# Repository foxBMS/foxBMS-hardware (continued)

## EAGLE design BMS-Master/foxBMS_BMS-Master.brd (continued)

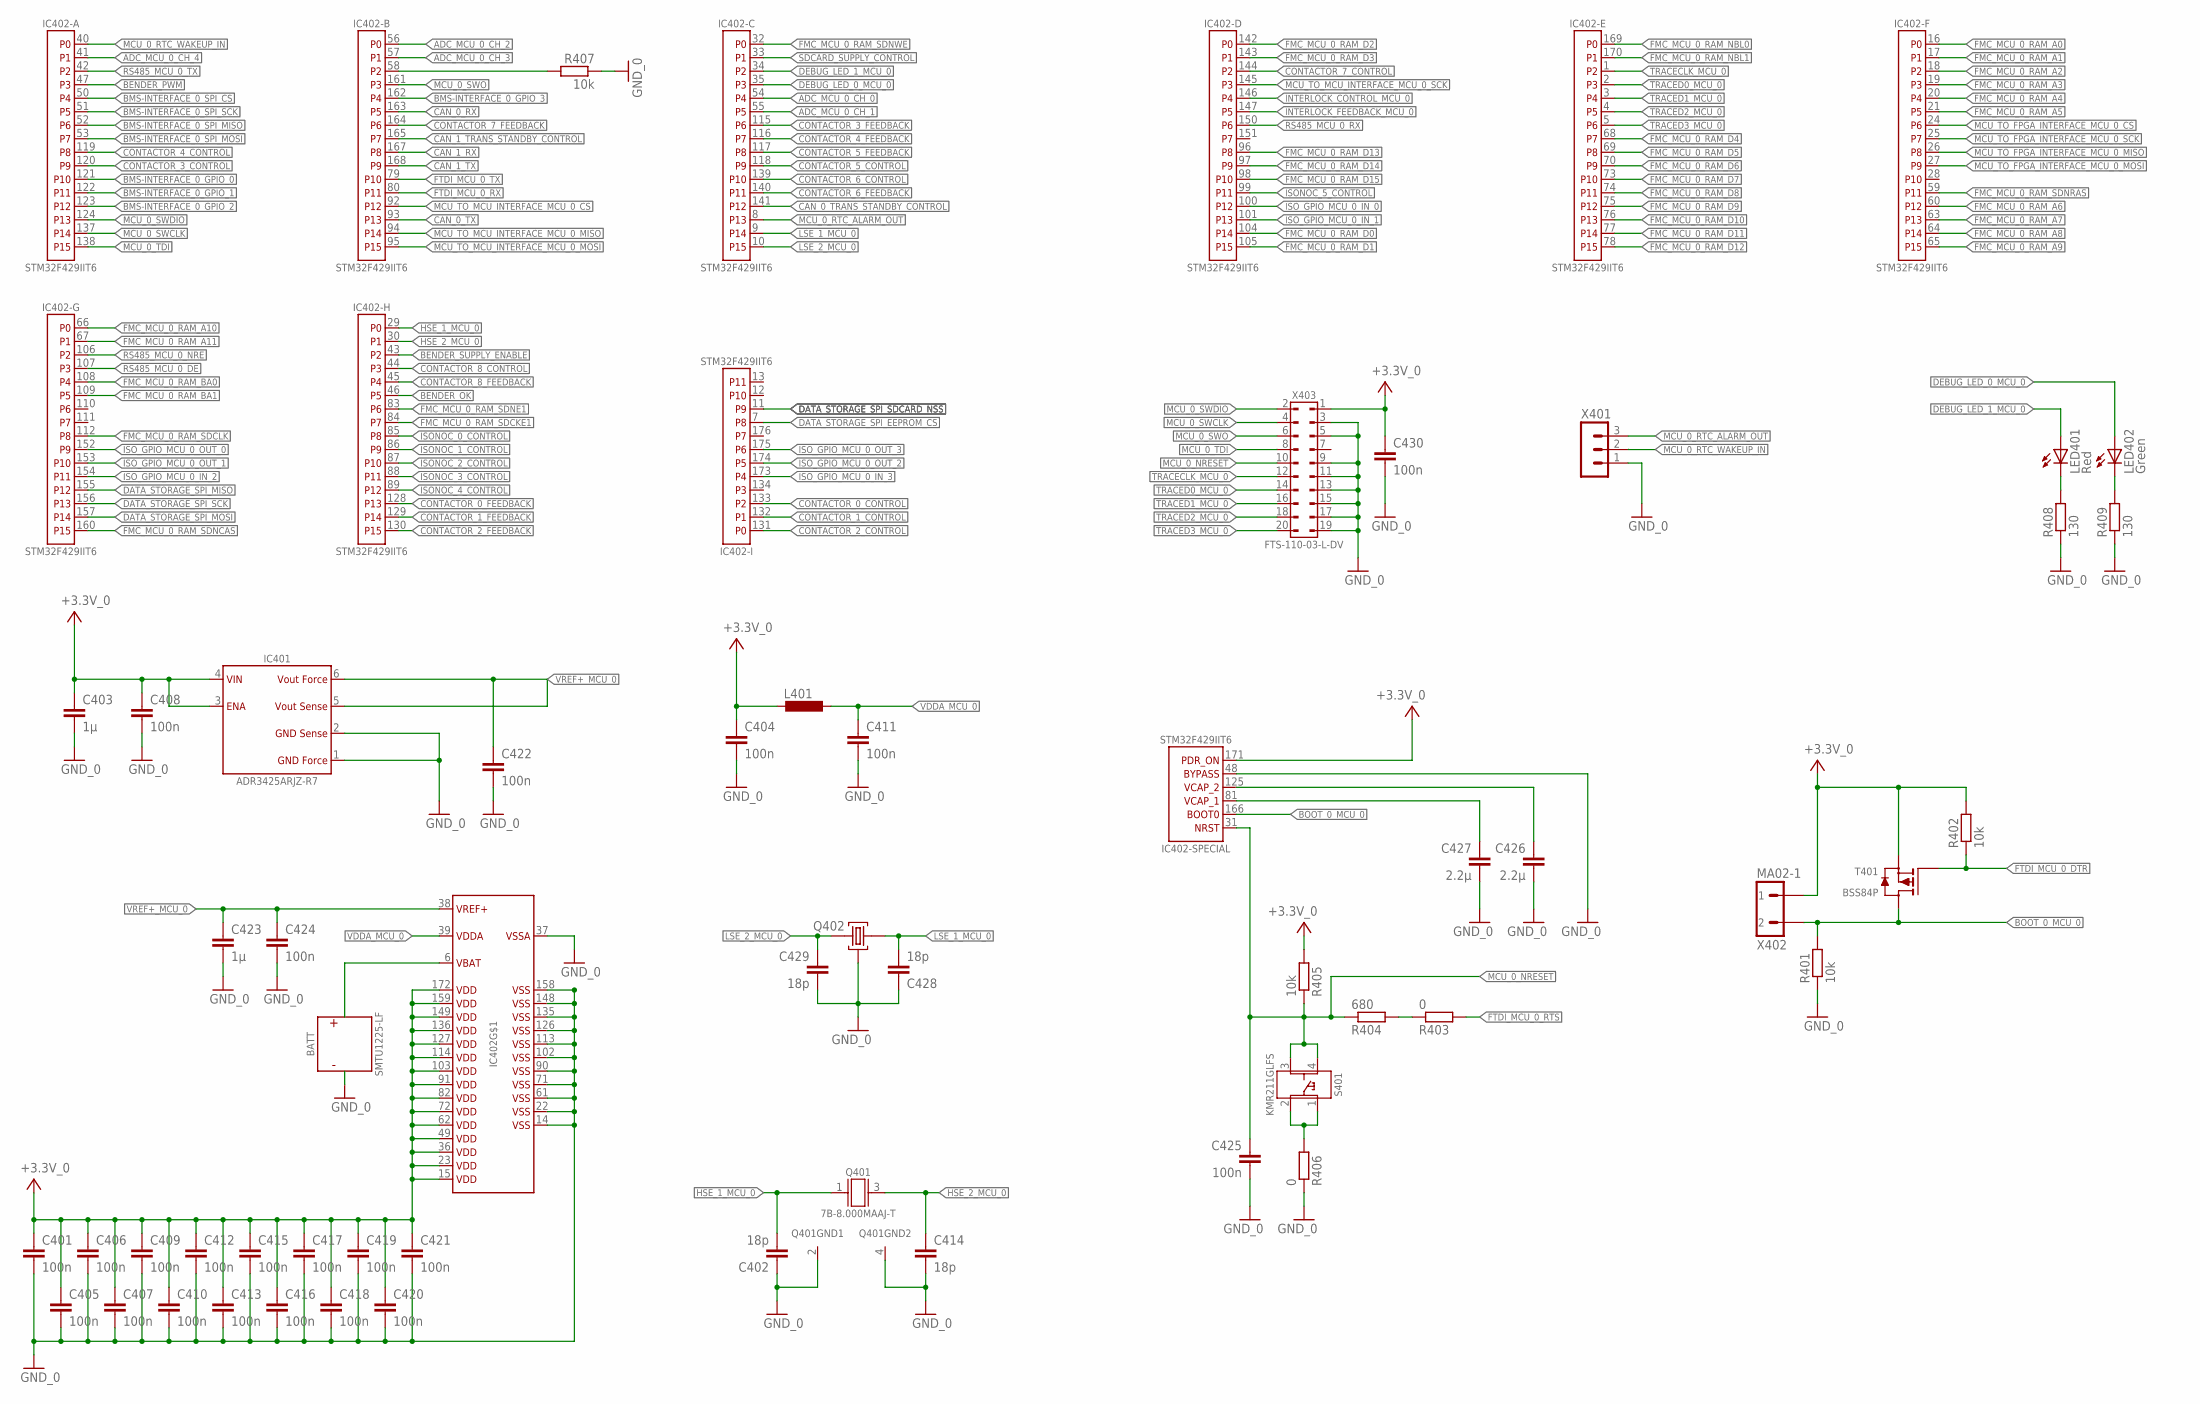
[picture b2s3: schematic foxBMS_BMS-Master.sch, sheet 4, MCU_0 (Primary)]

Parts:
BATT: SMTU1225-LF; X_SMD_(23,70MM_X_12,70MM_X_5,00MM)_R_RENATA_REV01
C401, C404, C405, C406, C407, C408, C409, C410, C411, C412, C413, C415, C416, C417, C418, C419, C420, C421, C422, C424, C425, C430: 100n; C0603
C402, C414, C428, C429: 18p; C0603
C403, C423: 1µ; C0603
C426, C427: 2.2µ; C0603
IC401: ADR3425ARJZ; IC_SMD_SOT23-6_(MO-178-AB)_R_AD_REV01
IC402: STM32F429IIT6; IC_SMD_LQFP176_R_ST_REV01
L401: L0805; 0805
LED401: Red; CHIP-LED0603
LED402: Green; CHIP-LED0603
Q401: 7B-8.000MAAJ-T; G_SMD_5,00MM_X_3,20MM_0,90MM_(7B)_TXC_REV01
Q402: MS3V; MS3V-T1R
R401, R402, R405, R407: 10k; R0603
R403, R406: 0; R0603
R404: 680; R0603
R408, R409: 130; R0603
S401: KMR211GLFS; S_SMD_4,60MMX2,80MMX1,90MM_R_CK-COMPONENTS_REV01
T401: BSS84P; V_SMD_SOT23_(TO-236AB)_R_INFINEON_REV01
X401: MA03-1
X402: MA02-1
X403: SAMTEC_FTS_20POL_HEADER_VERTIKAL_REV01; X_SMD_FTS_110-03_(20POL)_R_SAMTEC_REV01

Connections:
+3.3V_0: C401.1, C403.1, C404.1, C405.1, C406.1, C407.1, C408.1, C409.1, C410.1, C412.1, C413.1, C415.1, C416.1, C417.1, C418.1, C419.1, C420.1, C421.1, C430.1, IC401.3 (ENABLE), IC401.4 (VIN), IC402.15 (VDD1), IC402.23 (VDD2), IC402.36 (VDD3), IC402.49 (VDD4), IC402.62 (VDD5), IC402.72 (VDD6), IC402.82 (VDD7), IC402.91 (VDD8), IC402.103 (VDD9), IC402.114 (VDD10), IC402.127 (VDD11), IC402.136 (VDD12), IC402.149 (VDD13), IC402.159 (VDD14), IC402.171 (PDR_ON), IC402.172 (VDD15), L401.1, R402.2, R405.2, T401.2 (S), X402.1, X403.1; also elsewhere on the board
ADC_MCU_0_CH_0: IC402.54 (P4); also elsewhere on the board
ADC_MCU_0_CH_1: IC402.55 (P5); also elsewhere on the board
ADC_MCU_0_CH_2: IC402.56 (P0); also elsewhere on the board
ADC_MCU_0_CH_3: IC402.57 (P1); also elsewhere on the board
ADC_MCU_0_CH_4: IC402.41 (P1); also elsewhere on the board
BENDER_OK: IC402.46 (P5); also elsewhere on the board
BENDER_PWM: IC402.47 (P3); also elsewhere on the board
BENDER_SUPPLY_ENABLE: IC402.43 (P2); also elsewhere on the board
BMS-INTERFACE_0_GPIO_0: IC402.121 (P10); also elsewhere on the board
BMS-INTERFACE_0_GPIO_1: IC402.122 (P11); also elsewhere on the board
BMS-INTERFACE_0_GPIO_2: IC402.123 (P12); also elsewhere on the board
BMS-INTERFACE_0_GPIO_3: IC402.162 (P4); also elsewhere on the board
BMS-INTERFACE_0_SPI_CS: IC402.50 (P4); also elsewhere on the board
BMS-INTERFACE_0_SPI_MISO: IC402.52 (P6); also elsewhere on the board
BMS-INTERFACE_0_SPI_MOSI: IC402.53 (P7); also elsewhere on the board
BMS-INTERFACE_0_SPI_SCK: IC402.51 (P5); also elsewhere on the board
BOOT_0_MCU_0: IC402.166 (BOOT0), R401.2, T401.3 (D), X402.2
CAN_0_RX: IC402.163 (P5); also elsewhere on the board
CAN_0_TRANS_STANDBY_CONTROL: IC402.141 (P12); also elsewhere on the board
CAN_0_TX: IC402.93 (P13); also elsewhere on the board
CAN_1_RX: IC402.167 (P8); also elsewhere on the board
CAN_1_TRANS_STANDBY_CONTROL: IC402.165 (P7); also elsewhere on the board
CAN_1_TX: IC402.168 (P9); also elsewhere on the board
CONTACTOR_0_CONTROL: IC402.133 (P2); also elsewhere on the board
CONTACTOR_0_FEEDBACK: IC402.128 (P13); also elsewhere on the board
CONTACTOR_1_CONTROL: IC402.132 (P1); also elsewhere on the board
CONTACTOR_1_FEEDBACK: IC402.129 (P14); also elsewhere on the board
CONTACTOR_2_CONTROL: IC402.131 (P0); also elsewhere on the board
CONTACTOR_2_FEEDBACK: IC402.130 (P15); also elsewhere on the board
CONTACTOR_3_CONTROL: IC402.120 (P9); also elsewhere on the board
CONTACTOR_3_FEEDBACK: IC402.115 (P6); also elsewhere on the board
CONTACTOR_4_CONTROL: IC402.119 (P8); also elsewhere on the board
CONTACTOR_4_FEEDBACK: IC402.116 (P7); also elsewhere on the board
CONTACTOR_5_CONTROL: IC402.118 (P9); also elsewhere on the board
CONTACTOR_5_FEEDBACK: IC402.117 (P8); also elsewhere on the board
CONTACTOR_6_CONTROL: IC402.139 (P10); also elsewhere on the board
CONTACTOR_6_FEEDBACK: IC402.140 (P11); also elsewhere on the board
CONTACTOR_7_CONTROL: IC402.144 (P2); also elsewhere on the board
CONTACTOR_7_FEEDBACK: IC402.164 (P6); also elsewhere on the board
CONTACTOR_8_CONTROL: IC402.44 (P3); also elsewhere on the board
CONTACTOR_8_FEEDBACK: IC402.45 (P4); also elsewhere on the board
DATA_STORAGE_SPI_EEPROM_CS: IC402.7 (P8); also elsewhere on the board
DATA_STORAGE_SPI_MISO: IC402.155 (P12); also elsewhere on the board
DATA_STORAGE_SPI_MOSI: IC402.157 (P14); also elsewhere on the board
DATA_STORAGE_SPI_SCK: IC402.156 (P13); also elsewhere on the board
DATA_STORAGE_SPI_SDCARD_NSS: IC402.11 (P9); also elsewhere on the board
DEBUG_LED_0_MCU_0: IC402.35 (P3), LED402.A
DEBUG_LED_1_MCU_0: IC402.34 (P2), LED401.A
FMC_MCU_0_RAM_A0: IC402.16 (P0); also elsewhere on the board
FMC_MCU_0_RAM_A1: IC402.17 (P1); also elsewhere on the board
FMC_MCU_0_RAM_A2: IC402.18 (P2); also elsewhere on the board
FMC_MCU_0_RAM_A3: IC402.19 (P3); also elsewhere on the board
FMC_MCU_0_RAM_A4: IC402.20 (P4); also elsewhere on the board
FMC_MCU_0_RAM_A5: IC402.21 (P5); also elsewhere on the board
FMC_MCU_0_RAM_A6: IC402.60 (P12); also elsewhere on the board
FMC_MCU_0_RAM_A7: IC402.63 (P13); also elsewhere on the board
FMC_MCU_0_RAM_A8: IC402.64 (P14); also elsewhere on the board
FMC_MCU_0_RAM_A9: IC402.65 (P15); also elsewhere on the board
FMC_MCU_0_RAM_A10: IC402.66 (P0); also elsewhere on the board
FMC_MCU_0_RAM_A11: IC402.67 (P1); also elsewhere on the board
FMC_MCU_0_RAM_BA0: IC402.108 (P4); also elsewhere on the board
FMC_MCU_0_RAM_BA1: IC402.109 (P5); also elsewhere on the board
FMC_MCU_0_RAM_D0: IC402.104 (P14); also elsewhere on the board
FMC_MCU_0_RAM_D1: IC402.105 (P15); also elsewhere on the board
FMC_MCU_0_RAM_D2: IC402.142 (P0); also elsewhere on the board
FMC_MCU_0_RAM_D3: IC402.143 (P1); also elsewhere on the board
FMC_MCU_0_RAM_D4: IC402.68 (P7); also elsewhere on the board
FMC_MCU_0_RAM_D5: IC402.69 (P8); also elsewhere on the board
FMC_MCU_0_RAM_D6: IC402.70 (P9); also elsewhere on the board
FMC_MCU_0_RAM_D7: IC402.73 (P10); also elsewhere on the board
FMC_MCU_0_RAM_D8: IC402.74 (P11); also elsewhere on the board
FMC_MCU_0_RAM_D9: IC402.75 (P12); also elsewhere on the board
FMC_MCU_0_RAM_D10: IC402.76 (P13); also elsewhere on the board
FMC_MCU_0_RAM_D11: IC402.77 (P14); also elsewhere on the board
FMC_MCU_0_RAM_D12: IC402.78 (P15); also elsewhere on the board
FMC_MCU_0_RAM_D13: IC402.96 (P8); also elsewhere on the board
FMC_MCU_0_RAM_D14: IC402.97 (P9); also elsewhere on the board
FMC_MCU_0_RAM_D15: IC402.98 (P10); also elsewhere on the board
FMC_MCU_0_RAM_NBL0: IC402.169 (P0); also elsewhere on the board
FMC_MCU_0_RAM_NBL1: IC402.170 (P1); also elsewhere on the board
FMC_MCU_0_RAM_SDCKE1: IC402.84 (P7); also elsewhere on the board
FMC_MCU_0_RAM_SDCLK: IC402.112 (P8); also elsewhere on the board
FMC_MCU_0_RAM_SDNCAS: IC402.160 (P15); also elsewhere on the board
FMC_MCU_0_RAM_SDNE1: IC402.83 (P6); also elsewhere on the board
FMC_MCU_0_RAM_SDNRAS: IC402.59 (P11); also elsewhere on the board
FMC_MCU_0_RAM_SDNWE: IC402.32 (P0); also elsewhere on the board
FTDI_MCU_0_DTR: R402.1, T401.1 (G); also elsewhere on the board
FTDI_MCU_0_RTS: R403.2; also elsewhere on the board
FTDI_MCU_0_RX: IC402.80 (P11); also elsewhere on the board
FTDI_MCU_0_TX: IC402.79 (P10); also elsewhere on the board
GND_0: BATT.-, C401.2, C402.1, C403.2, C404.2, C405.2, C406.2, C407.2, C408.2, C409.2, C410.2, C411.2, C412.2, C413.2, C414.2, C415.2, C416.2, C417.2, C418.2, C419.2, C420.2, C421.2, C422.2, C423.2, C424.2, C425.2, C426.2, C427.2, C428.1, C429.2, C430.2, IC401.1 (GND_FORCE), IC401.2 (GND_SENSE), IC402.14 (VSS1), IC402.22 (VSS2), IC402.37 (VSSA), IC402.48 (BYPASS_REG), IC402.61 (VSS3), IC402.71 (VSS4), IC402.90 (VSS5), IC402.102 (VSS6), IC402.113 (VSS7), IC402.126 (VSS8), IC402.135 (VSS9), IC402.148 (VSS10), IC402.158 (VSS11), Q401.2 (GND), Q401.4 (GND), Q402.P$3 (2), R401.1, R406.1, R407.1, R408.1, R409.1, X401.1, X403.3, X403.5, X403.9, X403.11, X403.13, X403.15, X403.17, X403.19; also elsewhere on the board
HSE_1_MCU_0: C402.2, IC402.29 (P0), Q401.1 (A)
HSE_2_MCU_0: C414.1, IC402.30 (P1), Q401.3 (B)
INTERLOCK_CONTROL_MCU_0: IC402.146 (P4); also elsewhere on the board
INTERLOCK_FEEDBACK_MCU_0: IC402.147 (P5); also elsewhere on the board
ISONOC_0_CONTROL: IC402.85 (P8); also elsewhere on the board
ISONOC_1_CONTROL: IC402.86 (P9); also elsewhere on the board
ISONOC_2_CONTROL: IC402.87 (P10); also elsewhere on the board
ISONOC_3_CONTROL: IC402.88 (P11); also elsewhere on the board
ISONOC_4_CONTROL: IC402.89 (P12); also elsewhere on the board
ISONOC_5_CONTROL: IC402.99 (P11); also elsewhere on the board
ISO_GPIO_MCU_0_IN_0: IC402.100 (P12); also elsewhere on the board
ISO_GPIO_MCU_0_IN_1: IC402.101 (P13); also elsewhere on the board
ISO_GPIO_MCU_0_IN_2: IC402.154 (P11); also elsewhere on the board
ISO_GPIO_MCU_0_IN_3: IC402.173 (P4); also elsewhere on the board
ISO_GPIO_MCU_0_OUT_0: IC402.152 (P9); also elsewhere on the board
ISO_GPIO_MCU_0_OUT_1: IC402.153 (P10); also elsewhere on the board
ISO_GPIO_MCU_0_OUT_2: IC402.174 (P5); also elsewhere on the board
ISO_GPIO_MCU_0_OUT_3: IC402.175 (P6); also elsewhere on the board
LSE_1_MCU_0: C428.2, IC402.9 (P14), Q402.1
LSE_2_MCU_0: C429.1, IC402.10 (P15), Q402.2 (3)
MCU_0_NRESET: C425.1, IC402.31 (NRST), R404.1, R405.1, S401.3, S401.4, X403.10
MCU_0_RTC_ALARM_OUT: IC402.8 (P13), X401.3
MCU_0_RTC_WAKEUP_IN: IC402.40 (P0), X401.2
MCU_0_SWCLK: IC402.137 (P14), X403.4
MCU_0_SWDIO: IC402.124 (P13), X403.2
MCU_0_SWO: IC402.161 (P3), X403.6
MCU_0_TDI: IC402.138 (P15), X403.8
MCU_TO_FPGA_INTERFACE_MCU_0_CS: IC402.24 (P6); also elsewhere on the board
MCU_TO_FPGA_INTERFACE_MCU_0_MISO: IC402.26 (P8); also elsewhere on the board
MCU_TO_FPGA_INTERFACE_MCU_0_MOSI: IC402.27 (P9); also elsewhere on the board
MCU_TO_FPGA_INTERFACE_MCU_0_SCK: IC402.25 (P7); also elsewhere on the board
MCU_TO_MCU_INTERFACE_MCU_0_CS: IC402.92 (P12); also elsewhere on the board
MCU_TO_MCU_INTERFACE_MCU_0_MISO: IC402.94 (P14); also elsewhere on the board
MCU_TO_MCU_INTERFACE_MCU_0_MOSI: IC402.95 (P15); also elsewhere on the board
MCU_TO_MCU_INTERFACE_MCU_0_SCK: IC402.145 (P3); also elsewhere on the board
unnamed: C426.1, IC402.125 (VCAP_2)
unnamed: R406.2, S401.1, S401.2
unnamed: LED401.C, R408.2
unnamed: LED402.C, R409.2
unnamed: C427.1, IC402.81 (VCAP_1)
unnamed: IC402.58 (P2), R407.2
unnamed: R403.1, R404.2
unnamed: BATT.+, IC402.6 (VBAT)
RS485_MCU_0_DE: IC402.107 (P3); also elsewhere on the board
RS485_MCU_0_NRE: IC402.106 (P2); also elsewhere on the board
RS485_MCU_0_RX: IC402.150 (P6); also elsewhere on the board
RS485_MCU_0_TX: IC402.42 (P2); also elsewhere on the board
SDCARD_SUPPLY_CONTROL: IC402.33 (P1); also elsewhere on the board
TRACECLK_MCU_0: IC402.1 (P2), X403.12
TRACED0_MCU_0: IC402.2 (P3), X403.14
TRACED1_MCU_0: IC402.3 (P4), X403.16
TRACED2_MCU_0: IC402.4 (P5), X403.18
TRACED3_MCU_0: IC402.5 (P6), X403.20
VDDA_MCU_0: C411.1, IC402.39 (VDDA), L401.2
VREF+_MCU_0: C422.1, C423.1, C424.1, IC401.5 (VOUT_SENSE), IC401.6 (VOUT_FORCE), IC402.38 (VREF+)

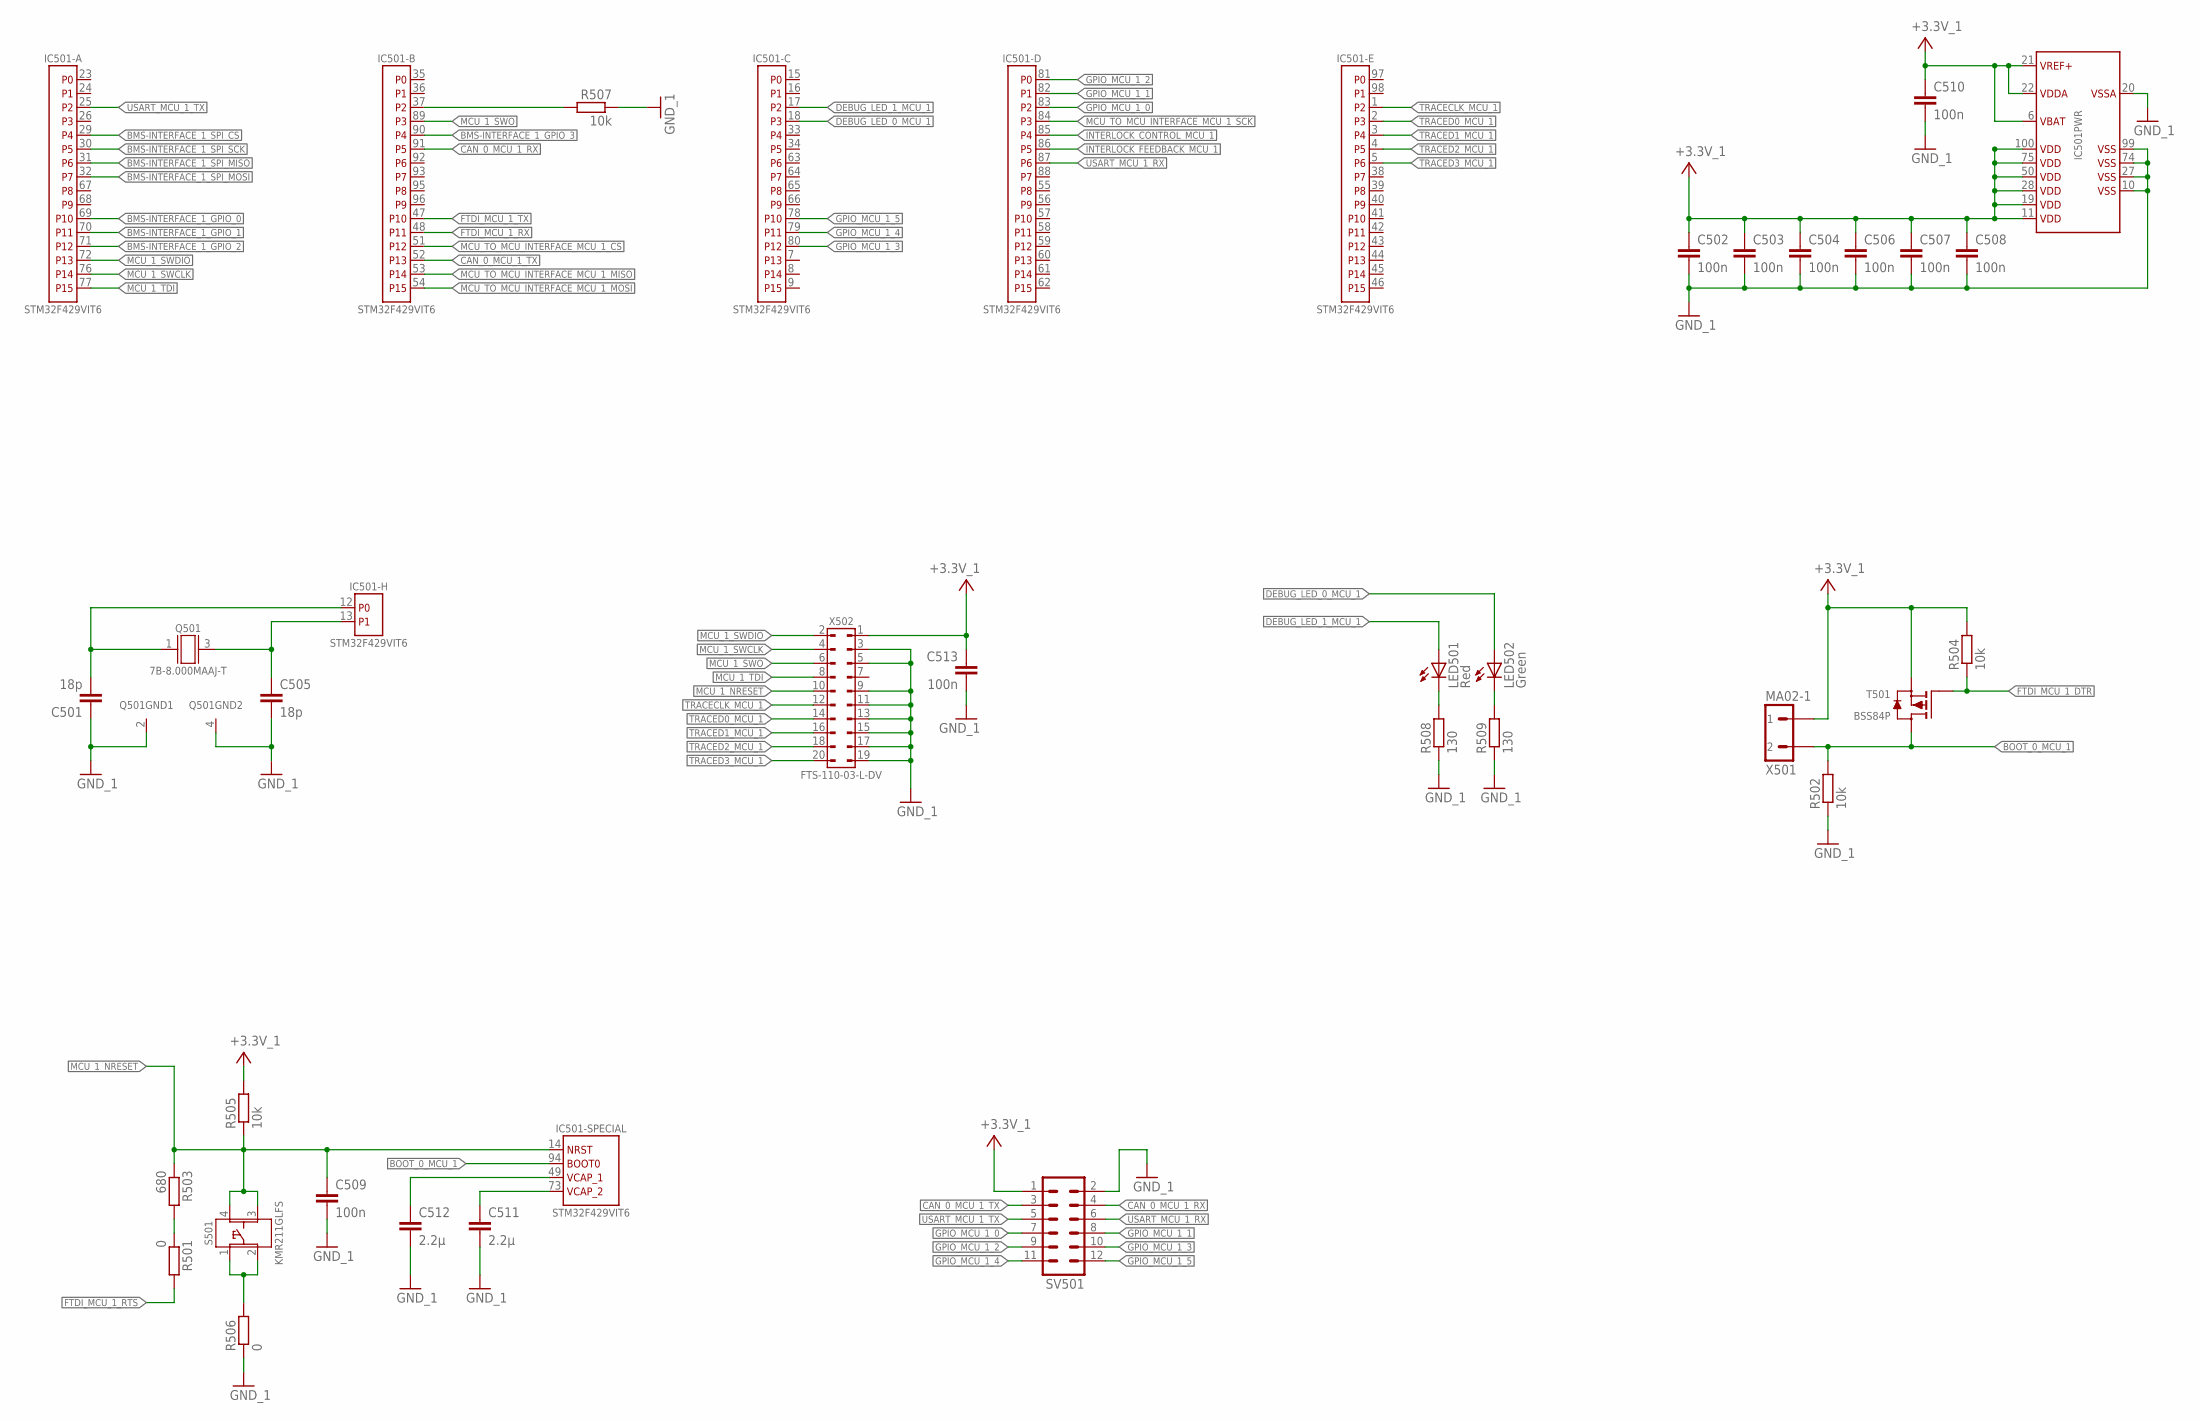
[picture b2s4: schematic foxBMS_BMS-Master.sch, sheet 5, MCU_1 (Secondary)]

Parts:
C501, C505: 18p; C0603
C502, C503, C504, C506, C507, C508, C509, C510, C513: 100n; C0603
C511, C512: 2.2µ; C0603
IC501: STM32F429VIT6; IC_SMD_LQFP100_R_ST_REV01
LED501: Red; CHIP-LED0603
LED502: Green; CHIP-LED0603
Q501: 7B-8.000MAAJ-T; G_SMD_5,00MM_X_3,20MM_0,90MM_(7B)_TXC_REV01
R501, R506: 0; R0603
R502, R504, R505, R507: 10k; R0603
R503: 680; R0603
R508, R509: 130; R0603
S501: KMR211GLFS; S_SMD_4,60MMX2,80MMX1,90MM_R_CK-COMPONENTS_REV01
SV501: MA06-2
T501: BSS84P; V_SMD_SOT23_(TO-236AB)_R_INFINEON_REV01
X501: MA02-1
X502: SAMTEC_FTS_20POL_HEADER_VERTIKAL_REV01; X_SMD_FTS_110-03_(20POL)_R_SAMTEC_REV01

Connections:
+3.3V_1: C502.1, C503.1, C504.1, C506.1, C507.1, C508.1, C510.1, C513.1, IC501.6 (VBAT), IC501.11 (VDD1), IC501.19 (VDD2), IC501.21 (VREF+), IC501.22 (VDDA), IC501.28 (VDD3), IC501.50 (VDD4), IC501.75 (VDD5), IC501.100 (VDD6), R504.2, R505.2, SV501.1, T501.2 (S), X501.1, X502.1; also elsewhere on the board
BMS-INTERFACE_1_GPIO_0: IC501.69 (P10); also elsewhere on the board
BMS-INTERFACE_1_GPIO_1: IC501.70 (P11); also elsewhere on the board
BMS-INTERFACE_1_GPIO_2: IC501.71 (P12); also elsewhere on the board
BMS-INTERFACE_1_GPIO_3: IC501.90 (P4); also elsewhere on the board
BMS-INTERFACE_1_SPI_CS: IC501.29 (P4); also elsewhere on the board
BMS-INTERFACE_1_SPI_MISO: IC501.31 (P6); also elsewhere on the board
BMS-INTERFACE_1_SPI_MOSI: IC501.32 (P7); also elsewhere on the board
BMS-INTERFACE_1_SPI_SCK: IC501.30 (P5); also elsewhere on the board
BOOT_0_MCU_1: IC501.94 (BOOT0), R502.2, T501.3 (D), X501.2
CAN_0_MCU_1_RX: IC501.91 (P5), SV501.4
CAN_0_MCU_1_TX: IC501.52 (P13), SV501.3
DEBUG_LED_0_MCU_1: IC501.18 (P3), LED502.A
DEBUG_LED_1_MCU_1: IC501.17 (P2), LED501.A
FTDI_MCU_1_DTR: R504.1, T501.1 (G); also elsewhere on the board
FTDI_MCU_1_RTS: R501.2; also elsewhere on the board
FTDI_MCU_1_RX: IC501.48 (P11); also elsewhere on the board
FTDI_MCU_1_TX: IC501.47 (P10); also elsewhere on the board
GND_1: C501.1, C502.2, C503.2, C504.2, C505.2, C506.2, C507.2, C508.2, C509.2, C510.2, C511.2, C512.2, C513.2, IC501.10 (VSS1), IC501.20 (VSSA), IC501.27 (VSS2), IC501.74 (VSS3), IC501.99 (VSS4), Q501.2 (GND), Q501.4 (GND), R502.1, R506.1, R507.1, R508.1, R509.1, SV501.2, X502.3, X502.5, X502.9, X502.11, X502.13, X502.15, X502.17, X502.19; also elsewhere on the board
GPIO_MCU_1_0: IC501.83 (P2), SV501.7
GPIO_MCU_1_1: IC501.82 (P1), SV501.8
GPIO_MCU_1_2: IC501.81 (P0), SV501.9
GPIO_MCU_1_3: IC501.80 (P12), SV501.10
GPIO_MCU_1_4: IC501.79 (P11), SV501.11
GPIO_MCU_1_5: IC501.78 (P10), SV501.12
INTERLOCK_CONTROL_MCU_1: IC501.85 (P4); also elsewhere on the board
INTERLOCK_FEEDBACK_MCU_1: IC501.86 (P5); also elsewhere on the board
MCU_1_NRESET: C509.1, IC501.14 (NRST), R503.1, R505.1, S501.3, S501.4, X502.10
MCU_1_SWCLK: IC501.76 (P14), X502.4
MCU_1_SWDIO: IC501.72 (P13), X502.2
MCU_1_SWO: IC501.89 (P3), X502.6
MCU_1_TDI: IC501.77 (P15), X502.8
MCU_TO_MCU_INTERFACE_MCU_1_CS: IC501.51 (P12); also elsewhere on the board
MCU_TO_MCU_INTERFACE_MCU_1_MISO: IC501.53 (P14); also elsewhere on the board
MCU_TO_MCU_INTERFACE_MCU_1_MOSI: IC501.54 (P15); also elsewhere on the board
MCU_TO_MCU_INTERFACE_MCU_1_SCK: IC501.84 (P3); also elsewhere on the board
unnamed: C501.2, IC501.12 (P0), Q501.1 (A)
unnamed: C505.1, IC501.13 (P1), Q501.3 (B)
unnamed: R506.2, S501.1, S501.2
unnamed: LED502.C, R509.2
unnamed: LED501.C, R508.2
unnamed: C511.1, IC501.73 (VCAP_2)
unnamed: C512.1, IC501.49 (VCAP_1)
unnamed: IC501.37 (P2), R507.2
unnamed: R501.1, R503.2
TRACECLK_MCU_1: IC501.1 (P2), X502.12
TRACED0_MCU_1: IC501.2 (P3), X502.14
TRACED1_MCU_1: IC501.3 (P4), X502.16
TRACED2_MCU_1: IC501.4 (P5), X502.18
TRACED3_MCU_1: IC501.5 (P6), X502.20
USART_MCU_1_RX: IC501.87 (P6), SV501.6
USART_MCU_1_TX: IC501.25 (P2), SV501.5

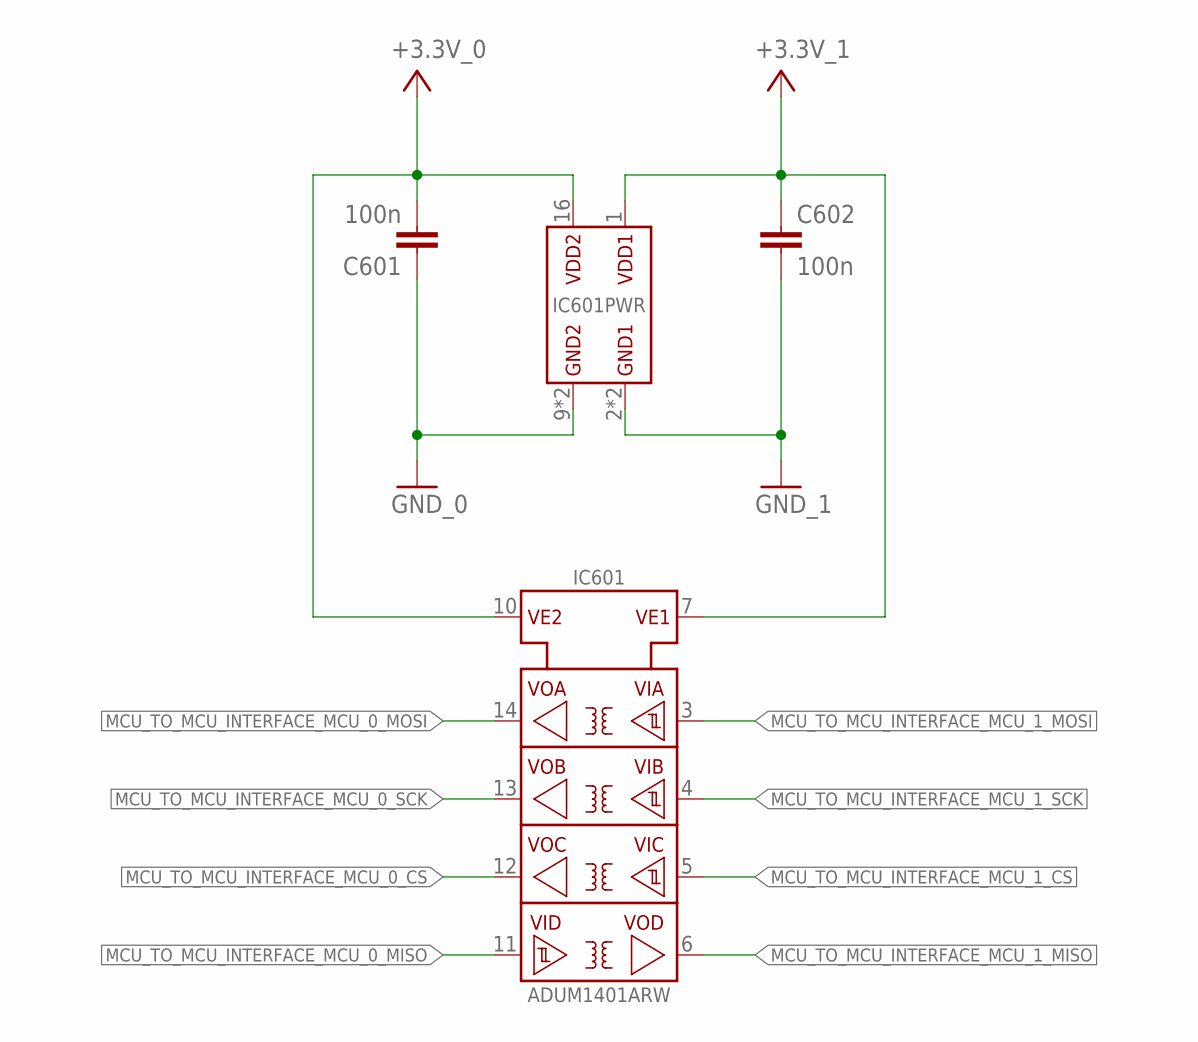
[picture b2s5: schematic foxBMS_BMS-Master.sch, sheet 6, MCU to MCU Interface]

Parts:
C601, C602: 100n; C0603
IC601: ADUM1401ARW; IC_SMD_SOIC-16_(JEDEC_MS-013-AA)_R_ANALOG_REV01

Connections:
+3.3V_0: C601.2, IC601.10 (VE2), IC601.16 (VDD2); also elsewhere on the board
+3.3V_1: C602.1, IC601.1 (VDD1), IC601.7 (VE1); also elsewhere on the board
GND_0: C601.1, IC601.9 (GND2), IC601.15 (GND2); also elsewhere on the board
GND_1: C602.2, IC601.2 (GND1), IC601.8 (GND1); also elsewhere on the board
MCU_TO_MCU_INTERFACE_MCU_0_CS: IC601.12 (VOC); also elsewhere on the board
MCU_TO_MCU_INTERFACE_MCU_0_MISO: IC601.11 (VID); also elsewhere on the board
MCU_TO_MCU_INTERFACE_MCU_0_MOSI: IC601.14 (VOA); also elsewhere on the board
MCU_TO_MCU_INTERFACE_MCU_0_SCK: IC601.13 (VOB); also elsewhere on the board
MCU_TO_MCU_INTERFACE_MCU_1_CS: IC601.5 (VIC); also elsewhere on the board
MCU_TO_MCU_INTERFACE_MCU_1_MISO: IC601.6 (VOD); also elsewhere on the board
MCU_TO_MCU_INTERFACE_MCU_1_MOSI: IC601.3 (VIA); also elsewhere on the board
MCU_TO_MCU_INTERFACE_MCU_1_SCK: IC601.4 (VIB); also elsewhere on the board

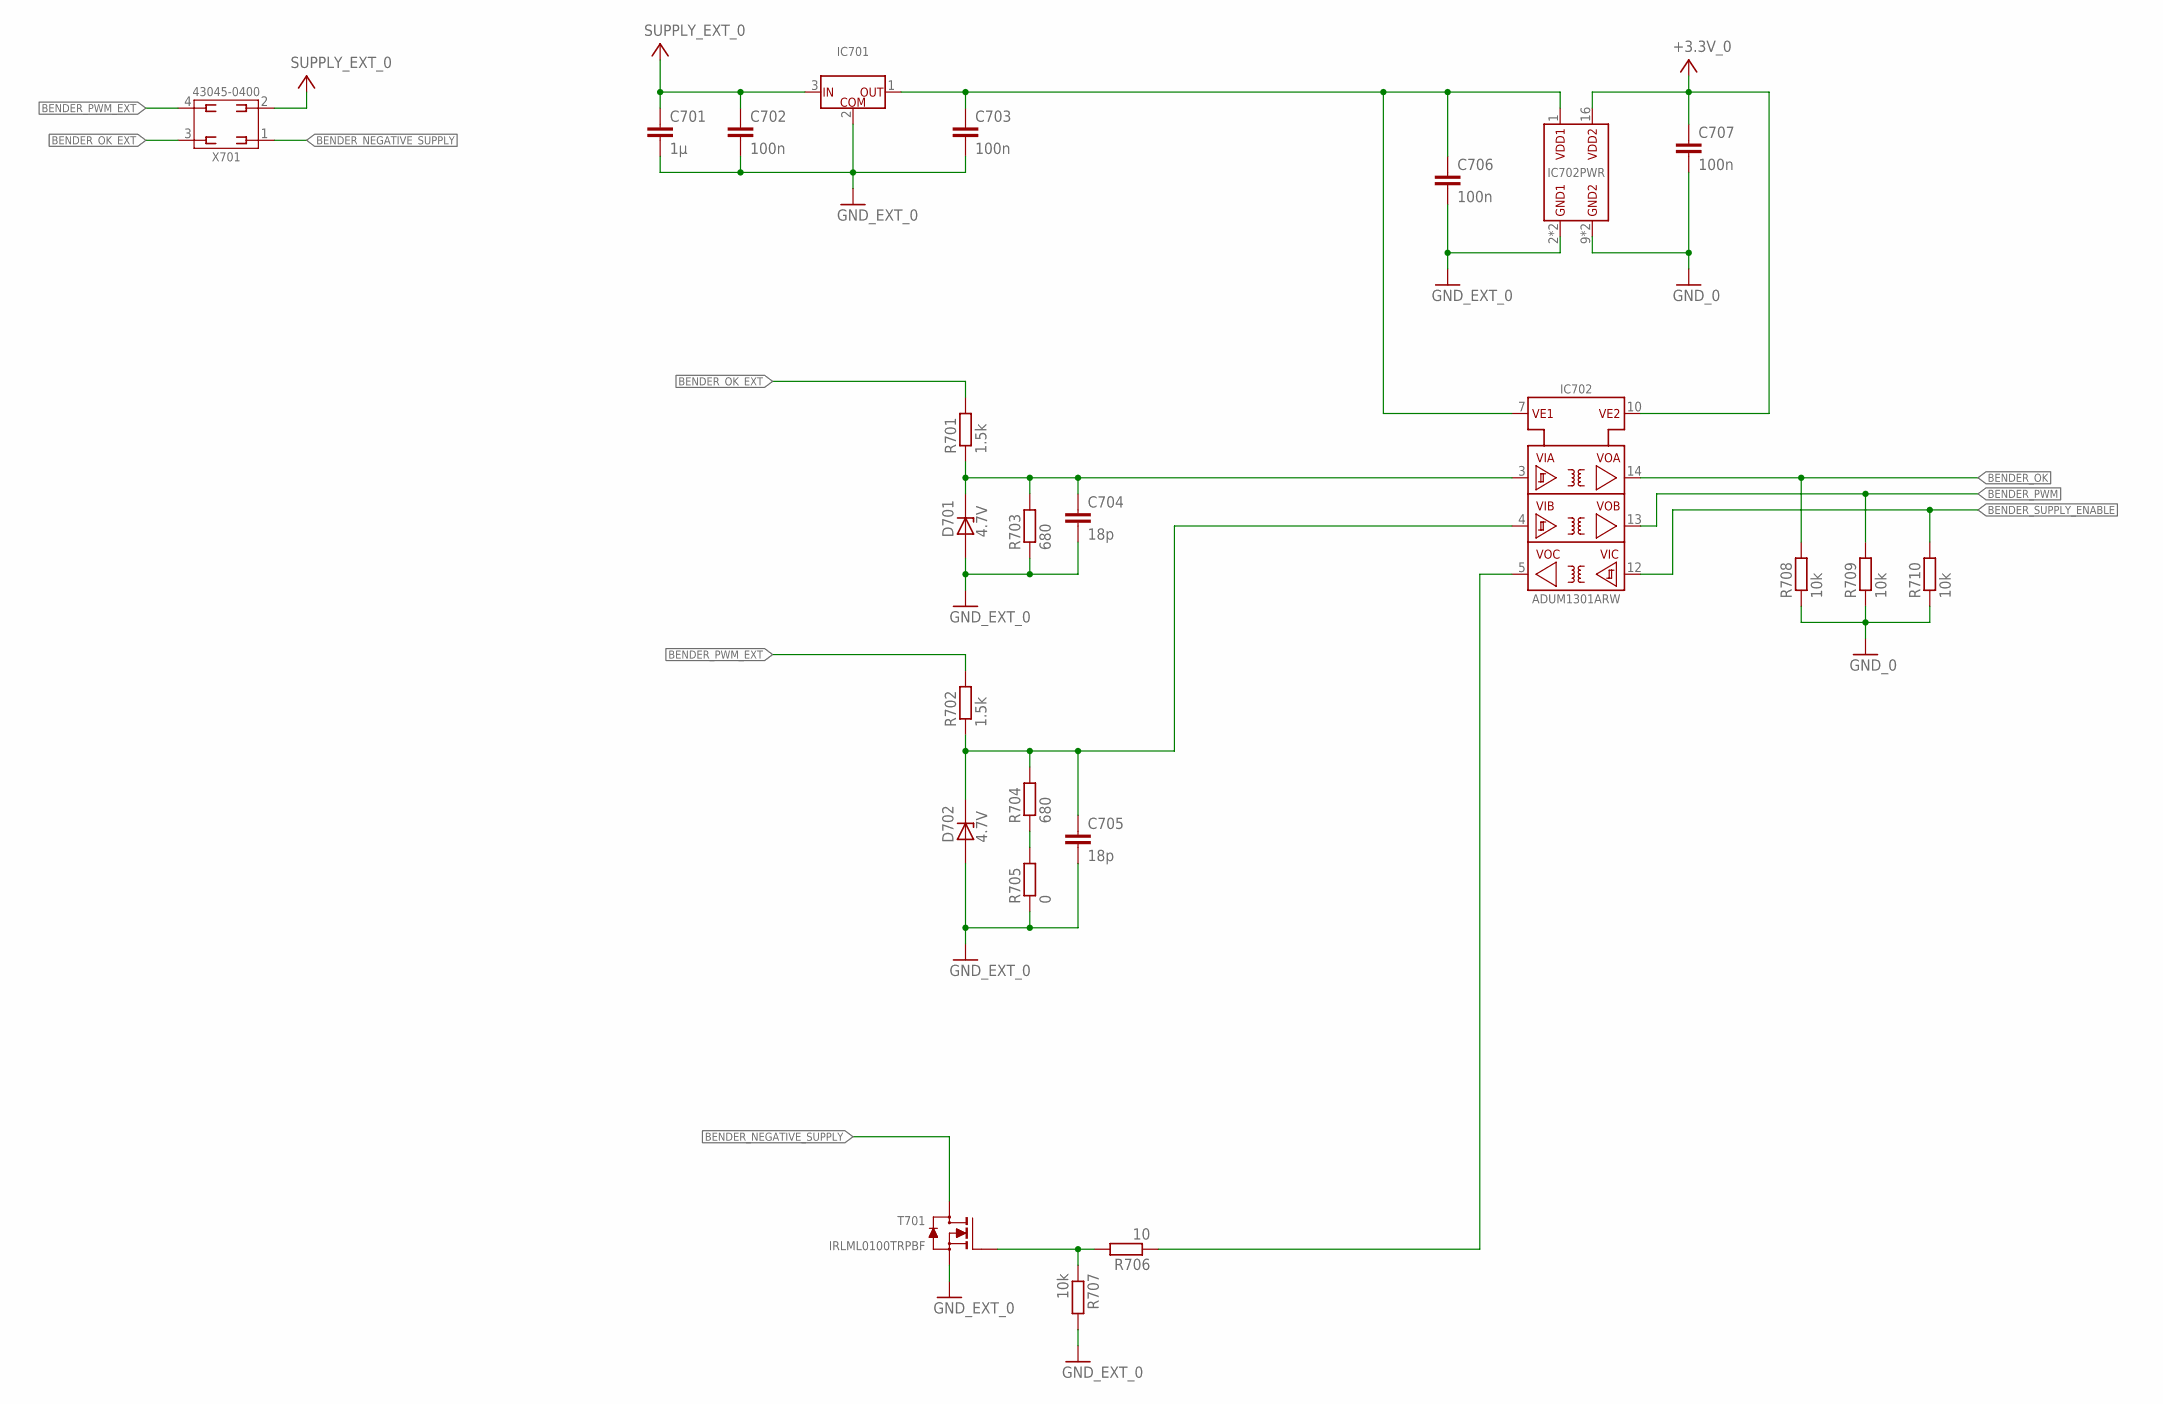
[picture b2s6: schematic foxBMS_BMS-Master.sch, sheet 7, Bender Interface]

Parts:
C701: 1µ; C0603
C702, C703, C706, C707: 100n; C0603
C704, C705: 18p; C0603
D701, D702: 4.7V; SOD323
IC701: UA78L05ACPK; IC_SMD_SOT-89_(SC-62/TO-243)_(R-PSSO-F3)_R_TI_REV01
IC702: ADUM1301ARW; IC_SMD_SOIC-16_(JEDEC_MS-013-AA)_R_ANALOG_REV01
R701, R702: 1.5k; R0603
R703, R704: 680; R0603
R705: 0; R0603
R706: 10; R0603
R707, R708, R709, R710: 10k; R0603
T701: IRLML0100TRPBF; V_SMD_SOT-23_(TO-236AB)_R_IR_REV01
X701: 43045-0400_MOLEX_4PIN; X_TH_MOLEX_43045-0400_R_REV01

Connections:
+3.3V_0: C707.1, IC702.10 (VE2), IC702.16 (VDD2); also elsewhere on the board
BENDER_ADUM_SUPPLY: C703.1, C706.1, IC701.1 (OUT), IC702.1 (VDD1), IC702.7 (VE1)
BENDER_NEGATIVE_SUPPLY: T701.3 (D), X701.1
BENDER_OK: IC702.14 (VOA), R708.2; also elsewhere on the board
BENDER_OK_EXT: R701.2, X701.3
BENDER_PWM: IC702.13 (VOB), R709.2; also elsewhere on the board
BENDER_PWM_EXT: R702.2, X701.4
BENDER_SUPPLY_ENABLE: IC702.12 (VIC), R710.2; also elsewhere on the board
GND_0: C707.2, IC702.9 (GND2), IC702.15 (GND2), R708.1, R709.1, R710.1; also elsewhere on the board
GND_EXT_0: C701.2, C702.2, C703.2, C704.2, C705.2, C706.2, D701.A, D702.A, IC701.2 (COM), IC702.2 (GND1), IC702.8 (GND1), R703.1, R705.1, R707.2, T701.2 (S); also elsewhere on the board
unnamed: IC702.5 (VOC), R706.1
unnamed: R706.2, R707.1, T701.1 (G)
unnamed: C705.1, D702.C (K), IC702.4 (VIB), R702.1, R704.2
unnamed: C704.1, D701.C (K), IC702.3 (VIA), R701.1, R703.2
unnamed: R704.1, R705.2
SUPPLY_EXT_0: C701.1, C702.1, IC701.3 (IN), X701.2; also elsewhere on the board
